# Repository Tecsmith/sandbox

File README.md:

# Sandbox

Various playthings :)

| | | |
|:--- |:---:|:--- |
| small-stm32 |  | STM32 based Seeed XIAO footprint module |
| `RX8130CE` |  | EPSON RX8130CE RTC QWIIC / STEMA-QT Module |
| ~~`DRV2605L`~~ | :x: | *Already commercially available [Sparkfun](https://www.sparkfun.com/sparkfun-haptic-motor-driver-drv2605l.html) ([source](https://github.com/sparkfun/Haptic_Motor_Driver)), and [Adafruit](https://www.adafruit.com/product/2305).* |

<!--
| `MCP3221`/`MCP3201` |||
-->

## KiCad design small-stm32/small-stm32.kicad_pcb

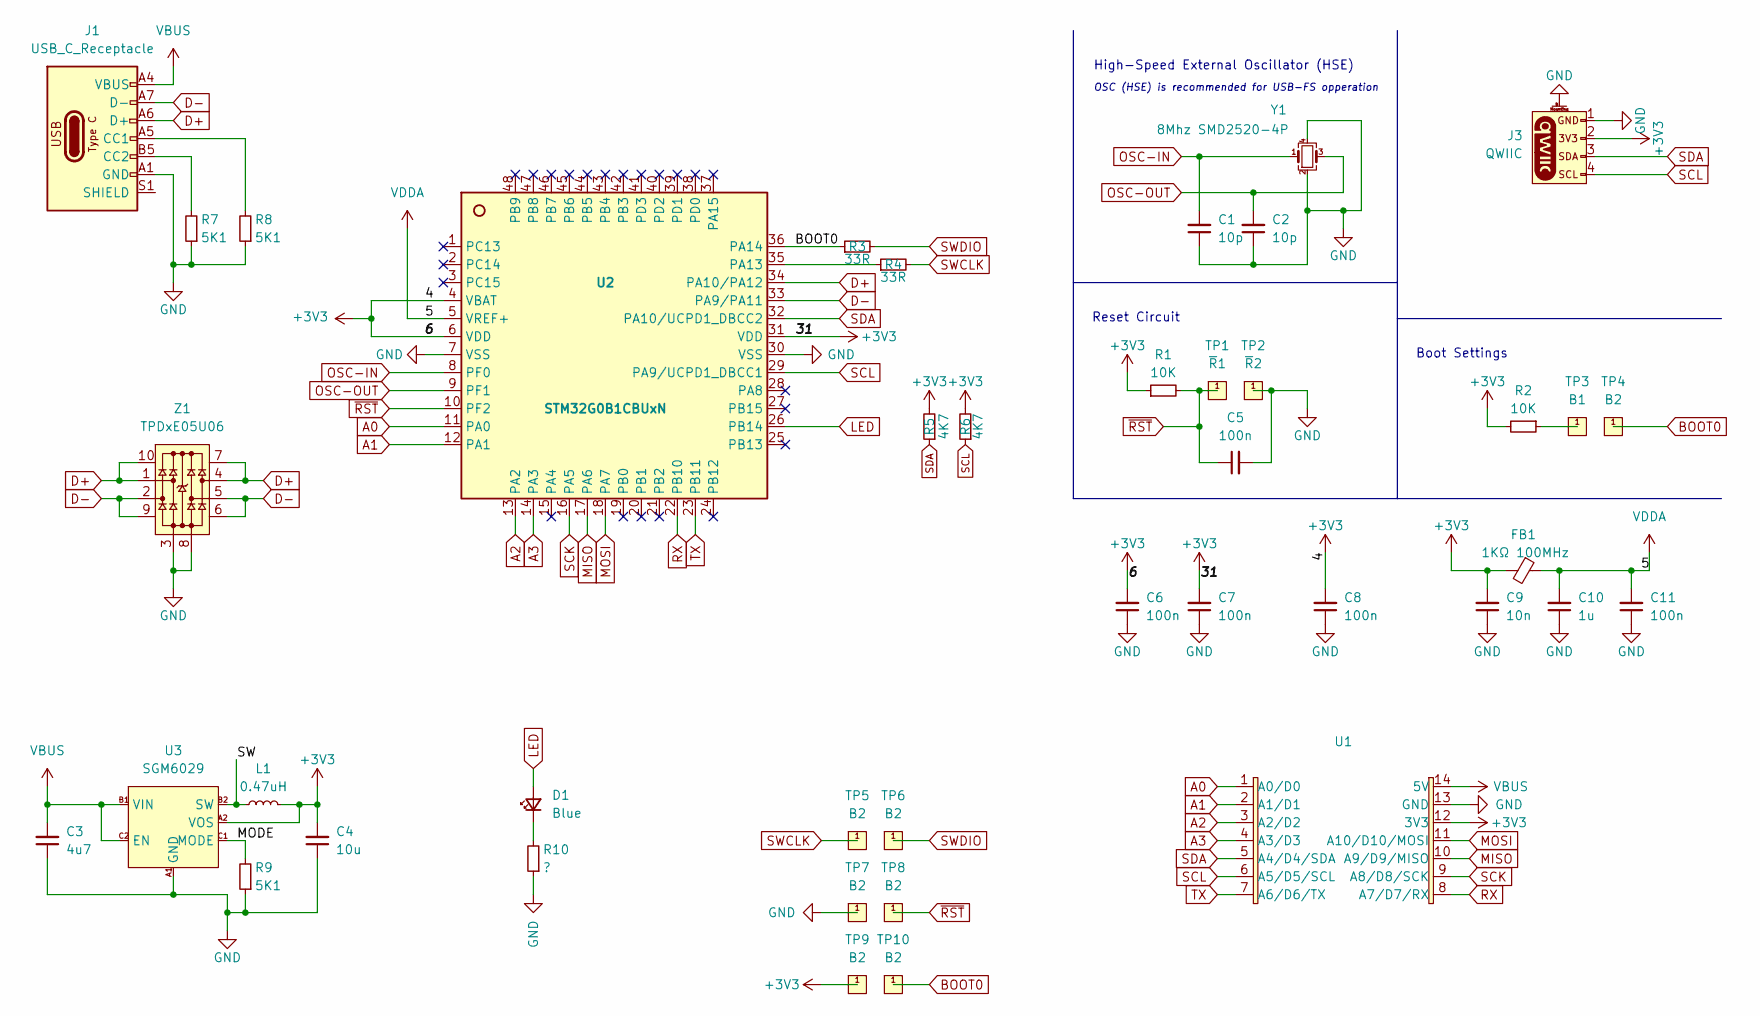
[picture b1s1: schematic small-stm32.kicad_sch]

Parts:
C1, C2: 10p; C_0402_1005Metric
C3: 4u7; C_0402_1005Metric
C4: 10u; C_0402_1005Metric
C5, C6, C7, C8, C11: 100n; C_0402_1005Metric
C9: 10n; C_0402_1005Metric
C10: 1u; C_0402_1005Metric
D1: Blue; LED_0402_1005Metric
FB1: 1KΩ 100MHz; L_0402_1005Metric; LCSC C13572
J1: USB_C_Receptacle; USB_C_Receptacle_HCTL_HC-TYPE-C-16P-01A
J3: QWIIC; JST_SH_SM04B-SRSS-TB_1x04-1MP_P1.00mm_Horizontal
L1: 0.47uH; L_0402_1005Metric
R1, R2: 10K; R_0402_1005Metric
R3, R4: 33R; R_0402_1005Metric
R5, R6: 4K7; R_0402_1005Metric
R7, R8, R9: 5K1; R_0402_1005Metric
R10: ?; R_0402_1005Metric
TP1: ~{R}1; TestPoint_Pad_D1.0mm
TP2: ~{R}2; TestPoint_Pad_D1.0mm
TP3: B1; TestPoint_Pad_D1.0mm
TP4: B2; TestPoint_Pad_D1.0mm
TP5, TP6, TP7, TP8, TP9, TP10: B2; TestPoint_Pad_D1.5mm
U1: MOUDLE14-XIAO-HALF-HOLE
U2: STM32G0B1CBUxN; QFN-48-1EP_7x7mm_P0.5mm_EP5.6x5.6mm
U3: SGM6029; WLCSP-0.74×1.09-6B
Y1: 8Mhz SMD2520-4P; Crystal_SMD_2520-4Pin_2.5x2.0mm
Z1: TPDxE05U06; UFDFN-10_2.5x1.0mm_P0.5mm

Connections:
+3V3: C4.2, C6.2, C7.2, C8.2, C9.2, FB1.2, J3.2, L1.2, R1.1, R2.2, R5.2, R6.2, TP9.1, U1.12 (3V3), U2.4 (VBAT), U2.6 (VDD), U2.31 (VDD), U3.A2 (VOS)
/MODE: R9.2, U3.C1 (MODE)
/SW: L1.1, U3.B2 (SW)
A0: U1.1 (A0/D0), U2.11 (PA0)
A1: U1.2 (A1/D1), U2.12 (PA1)
A2: U1.3 (A2/D2), U2.13 (PA2)
A3: U1.4 (A3/D3), U2.14 (PA3)
BOOT0: R3.1, TP4.1, TP10.1, U2.36 (PA14)
D+: J1.A6 (D+), J1.B6 (D+), U2.34 (PA10/PA12), Z1.1, Z1.4, Z1.7, Z1.10
D-: J1.A7 (D-), J1.B7 (D-), U2.33 (PA9/PA11), Z1.2, Z1.5, Z1.6, Z1.9
GND: C1.1, C2.1, C3.1, C4.1, C5.2, C6.1, C7.1, C8.1, C9.1, C10.1, C11.1, J1.A1 (GND), J1.A12 (GND), J1.B1 (GND), J1.B12 (GND), J3.1, J3.MP, R7.1, R8.1, R9.1, R10.1, TP2.1, TP7.1, U1.13 (GND), U2.7 (VSS), U2.30 (VSS), U3.A1 (GND), Y1.2, Y1.4, Z1.3, Z1.8
LED: D1.2 (A), U2.26 (PB14)
MISO: U1.10 (A9/D9/MISO), U2.17 (PA6)
MOSI: U1.11 (A10/D10/MOSI), U2.18 (PA7)
unnamed: D1.1 (K), R10.2
unnamed: J1.A5 (CC1), R8.2
unnamed: J1.B5 (CC2), R7.2
unnamed: R2.1, TP3.1
unnamed: R4.1, U2.35 (PA13)
OSC-IN: C1.2, U2.8 (PF0), Y1.1
OSC-OUT: C2.2, U2.9 (PF1), Y1.3
RX: U1.8 (A7/D7/RX), U2.22 (PB10)
SCK: U1.9 (A8/D8/SCK), U2.16 (PA5)
SCL: J3.4, R6.1, U1.6 (A5/D5/SCL), U2.29 (PA9/UCPD1_DBCC1)
SDA: J3.3, R5.1, U1.5 (A4/D4/SDA), U2.32 (PA10/UCPD1_DBCC2)
SWCLK: R4.2, TP5.1
SWDIO: R3.2, TP6.1
TX: U1.7 (A6/D6/TX), U2.23 (PB11)
VBUS: C3.2, J1.A4 (VBUS), J1.A9 (VBUS), J1.B4 (VBUS), J1.B9 (VBUS), U1.14 (5V), U3.B1 (VIN), U3.C2 (EN)
VDDA: C10.2, C11.2, FB1.1, U2.5 (VREF+)
~RST: C5.1, R1.2, TP1.1, TP8.1, U2.10 (PF2)

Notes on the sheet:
Boot Settings
Reset Circuit
OSC (HSE) is recommended for USB-FS opperation
High-Speed External Oscillator (HSE)

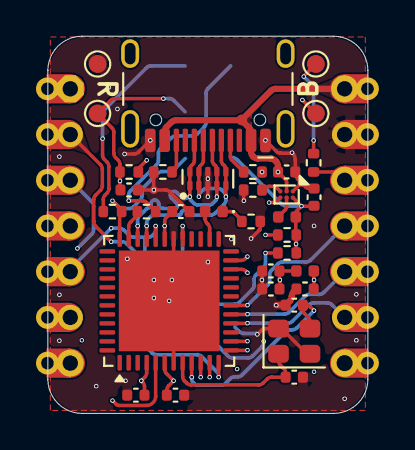
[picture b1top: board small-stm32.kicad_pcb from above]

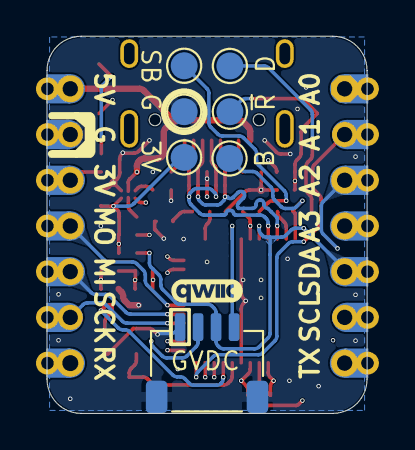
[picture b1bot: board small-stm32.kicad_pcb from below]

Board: 4 copper layers, 17.8 x 21.0 mm, 41 parts (7 on the bottom side), 31 nets.

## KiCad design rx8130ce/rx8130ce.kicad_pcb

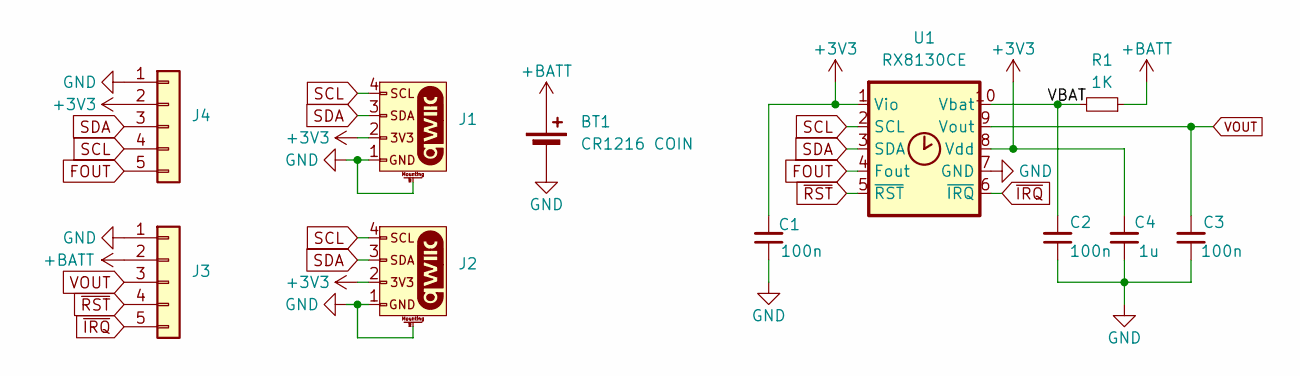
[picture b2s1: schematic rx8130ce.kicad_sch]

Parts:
BT1: CR1216 COIN; BatteryHolder_Keystone_3000_1x12mm
C1, C2, C3: 100n; C_0603_1608Metric
C4: 1u; C_0603_1608Metric
J1, J2: JST_SH_SM04B-SRSS-TB_1x04-1MP_P1.00mm_Horizontal
J3, J4: Conn_01x05; 1x05_P2.54mm
R1: 1K; R_0603_1608Metric
U1: RX8130CE; rx8130ce

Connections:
+3V3: C1.2, C4.2, J1.2, J2.2, J4.2, U1.1 (Vio), U1.8 (Vdd)
+BATT: BT1.1 (+), J3.2, R1.1
/VBAT: C2.2, R1.2, U1.10 (Vbat)
FOUT: J4.5, U1.4 (Fout)
GND: BT1.2 (-), C1.1, C2.1, C3.1, C4.1, J1.1, J1.MP, J2.1, J2.MP, J3.1, J4.1, U1.7 (GND)
SCL: J1.4, J2.4, J4.4, U1.2 (SCL)
SDA: J1.3, J2.3, J4.3, U1.3 (SDA)
VOUT: C3.2, J3.3, U1.9 (Vout)
~IRQ: J3.5, U1.6 (~IRQ)
~RST: J3.4, U1.5 (~RST)

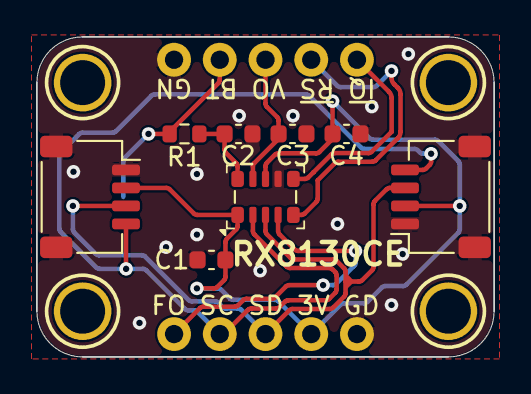
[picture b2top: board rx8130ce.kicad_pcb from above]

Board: 2 copper layers, 25.4 x 17.8 mm, 11 parts (1 on the bottom side), 10 nets.

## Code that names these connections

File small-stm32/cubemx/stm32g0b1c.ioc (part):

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Mcu.Name=STM32G0B1C(B-C-E)UxN
Mcu.Package=UFQFPN48
Mcu.UserName=STM32G0B1CBUxN
PA0.GPIOParameters=GPIO_Label
PA0.GPIO_Label=A0
PA0.Mode=IN0
PA0.Signal=ADC1_IN0
PA1.GPIOParameters=GPIO_Label
PA1.GPIO_Label=A1
PA1.Mode=IN1
PA1.Signal=ADC1_IN1
PA10.GPIOParameters=GPIO_Label
PA10.GPIO_Label=SDA
PA10.Mode=I2C
PA10.Signal=I2C1_SDA
PA11\ [PA9].GPIOParameters=GPIO_Label
PA11\ [PA9].GPIO_Label=D-
PA11\ [PA9].Mode=Device
PA11\ [PA9].Signal=USB_DM
PA12\ [PA10].GPIOParameters=GPIO_Label
PA12\ [PA10].GPIO_Label=D+
PA12\ [PA10].Mode=Device
PA12\ [PA10].Signal=USB_DP
PA13.GPIOParameters=GPIO_Label
PA13.GPIO_Label=SWDIO
PA13.Mode=Serial_Wire
PA13.Signal=SYS_SWDIO
PA14-BOOT0.GPIOParameters=GPIO_Label
PA14-BOOT0.GPIO_Label=SWCLK
PA14-BOOT0.Mode=Serial_Wire
PA14-BOOT0.Signal=SYS_SWCLK
PA2.GPIOParameters=GPIO_Label
PA2.GPIO_Label=A2
PA2.Mode=IN2
PA2.Signal=ADC1_IN2
PA3.GPIOParameters=GPIO_Label
PA3.GPIO_Label=A3
PA3.Mode=IN3
PA3.Signal=ADC1_IN3
PA5.GPIOParameters=GPIO_Label
PA5.GPIO_Label=SCK
PA5.Mode=Full_Duplex_Master
PA5.Signal=SPI1_SCK
PA6.GPIOParameters=GPIO_Label
PA6.GPIO_Label=MISO
PA6.Mode=Full_Duplex_Master
PA6.Signal=SPI1_MISO
PA7.GPIOParameters=GPIO_Label
PA7.GPIO_Label=MOSI
PA7.Mode=Full_Duplex_Master
PA7.Signal=SPI1_MOSI
PA9.GPIOParameters=GPIO_Label
PA9.GPIO_Label=SCL
PA9.Mode=I2C
PA9.Signal=I2C1_SCL
PB10.GPIOParameters=GPIO_Label
PB10.GPIO_Label=RX
PB10.Mode=Asynchronous
PB10.Signal=LPUART1_RX
PB11.GPIOParameters=GPIO_Label
PB11.GPIO_Label=TX
PB11.Mode=Asynchronous
PB11.Signal=LPUART1_TX
PF0-OSC_IN\ (PF0).Mode=HSE-External-Oscillator
PF0-OSC_IN\ (PF0).Signal=RCC_OSC_IN
PF1-OSC_OUT\ (PF1).Mode=HSE-External-Oscillator
PF1-OSC_OUT\ (PF1).Signal=RCC_OSC_OUT
RCC.HSE_VALUE=8000000
RCC.SYSCLKFreq_VALUE=16000000
board=custom

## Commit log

2025-12-02 init up
2025-12-08 update-2025-12-08
2026-04-18 bump to KiCAD 10
